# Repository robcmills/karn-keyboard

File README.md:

# karn-keyboard

Split, ortholinear, non-staggered, 38 key keyboard.

What makes the Karn unique are the 1.5u thumb arc and pinky reach keys.

### Thumb Arc Keys

I didn't like "tucking" my thumb under my palm, and most other keyboards I found in this "Ferris" family of split, minimal keyboards have thumb keys located "inside" of the homing fj keys' column. 

The Karn aligns the inner thumb key with the homing column. This feels comfortable to me, and provides a sense of "homing" to my thumbs as well. With the additional thumb keys splaying out inwards from there, in a more aggresive downward arc than the Ferris. This arc follows the natural arc of my thumb. I took photos and did measurements.

Also, the thumb keys are designed for vertical 1.5u keycaps. This is because I found 1u keycaps uncomfortable for my thumbs, as I typically make contact with the side of my thumb, which has more surface area making contact, and the sharp edge of 1u keycaps would dig into the center of the area of skin making contact. 

Other keyboards are designed with maybe one or two larger thumb keys, but they are typically 2u, which means the added complexity of stabilizers, in addition to just feeling too big.

### Pinky Reach Keys

"Pinky reach" meaning the keys in the colmn "outside" of the pinky column. On a traditional keyboard this would correspond to the Escape, Tab, Caps-lock, and Shift keys on the left hand for example. The other keyboard designs I saw either had no pinky reach keys, or a full set of three or four. The Karn is designed very much in the "all keys within one key distance of home" style, as is common in the less than 40% category. However, although the pinky diagonal reaches technically still count as "one key distance", that reach felt too difficult to me. And so they are omitted, but having zero pinky reach keys, I found it difficult to fit Tab and Enter elsewhere. There were just too few keys at that point, and so I wanted to retain a single horizontal pinky reach key on each side. I use these for Tab (left), Enter (right), and hold for Hyper. 

### Versions

There are actually two versions in this repo: 

### Karn-1

The original version is designed to be wireless. It is built around a standard 24 pin microcontroller with bluetooth support. I used the Nice-Nano-v2. With only 24 pins and 38 keys, this necessitated a matrix key layout, with diodes. Additionally, it adds an on/off switch, reset switch, and battery connector. This makes assembly much more complicated. Especially the diodes, which are super tiny, and very difficult to hot-air solder onto the tiny pads. This is not for beginners.

Also, the original karn pcb is split across two different designs, one for the left and another for the right. This doubles manufactoring costs, since you have to order the pcbs for both sides. I was learning.

### Karn-2

The karn-2 seeks to improve on the original with a host of simplifications. It is built around a 40 pin microcontroller so that there is no need for a key matrix, and hence no diodes. Furthermore, the microcontroller I found has a reset switch built onto the board, so no extra parts and hot-air soldering required. The microcontroller does not support Bluetooth, but this means no battery connector and no on/off switch. This greatly simplifies the design and assembly, and reduces the number of parts required and thus the cost.

And lastly, the karn-2 PCB is designed to be reversible, so you only need to order it once, and you can use it for both left and right. 

### Parts List

- key switches
https://mkultra.click/choc-switches
Kailh Low Profile Choc v1

- key caps
https://mkultra.click/mbk-choc-keycaps

- microcontroller (karn-1)
https://mkultra.click/nice-nano-v2/
(includes 301230 110mAh Battery with JST Connector) 

- microcontroller (karn-2)
https://www.digikey.com/en/products/detail/dfrobot/DFR0864/14824968
DFRobot Blackpill development board

- microcontroller sockets and pins (karn-1)
https://mkultra.click/mill-max-micro-controller-sockets-and-pins/

- microcontroller sockets and pins (karn-2)
https://www.digikey.com/en/products/detail/mill-max-manufacturing-corp/315-43-120-41-003000/4455248
Mill-max 315-43-120-41-003000 sockets
https://www.digikey.com/en/products/detail/mill-max-manufacturing-corp/3320-1-00-15-00-00-03-0/4147393
Mill-max 3320-1-00-15-00-00-03-0 pins

- trrs jack
https://mkultra.click/pj-320a-3-5mm-trrs-jack/

- power switches (karn-1)
https://mkultra.click/alps-ssss811101/
https://tech.alpsalpine.com/e/products/detail/SSSS811101/

- diodes (karn-1)
https://www.digikey.com/en/products/detail/micro-commercial-co/1N4148X-TP/789328
PART: 1N4148XTPMSCT-ND
MFG : MICRO COMMERCIAL CO (VA) / 1N4148X-TP
DESC: DIODE GEN PURP 75V 150MA SOD523
UNIT PRICE: $0.173

- leds (karn-1)
https://www.digikey.com/en/products/detail/adafruit-industries-llc/2686/5804107
PART: 1528-1541-ND
MFG : ADAFRUIT INDUSTRIES LLC / 2686
DESC: ADDRESS LED DISC SERIAL RGB 10PK
UNIT PRICE: $4.95 (for quantity 10)

- battery connectors (karn-1)
https://www.digikey.com/en/products/detail/jst-sales-america-inc/S2B-PH-K-S-LF-SN/926626
PART: 455-1719-ND
MFG : JST SALES AMERICA INC / S2B-PH-K-S(LF)(SN)
DESC: CONN HEADER R/A 2POS 2MM
UNIT PRICE: $0.134

- reset switches (karn-1)
https://www.digikey.com/en/products/detail/e-switch/TL3313AF250QG/4029401
PART: EG6065CT-ND
MFG : E-SWITCH (VA) / TL3313AF250QG
DESC: SWITCH TACTILE SPST-NO 0.05A 12V
UNIT PRICE: $0.431

- feet
Self-Adhesive Clear Rubber Feet Tiny Bumpons (6x2mm)
https://www.amazon.com/dp/B06XCNM69B

- pcb
https://www.pcbway.com/

### Firmware

https://github.com/robcmills/karn-keyboard-firmware

### Inspiration

#### Thumb Block Style

- Maltron https://en.wikipedia.org/wiki/Maltron

- Kinesis Advantage https://kinesis-ergo.com/shop/advantage2/

- Ergodox EZ https://ergodox-ez.com/

#### Thumb Arc Style

- NEC PWP http://xahlee.info/kbd/nec_pc-8801_keyboard.html

- Kyria https://blog.splitkb.com/blog/introducing-the-kyria

- Corne https://github.com/foostan/crkbd

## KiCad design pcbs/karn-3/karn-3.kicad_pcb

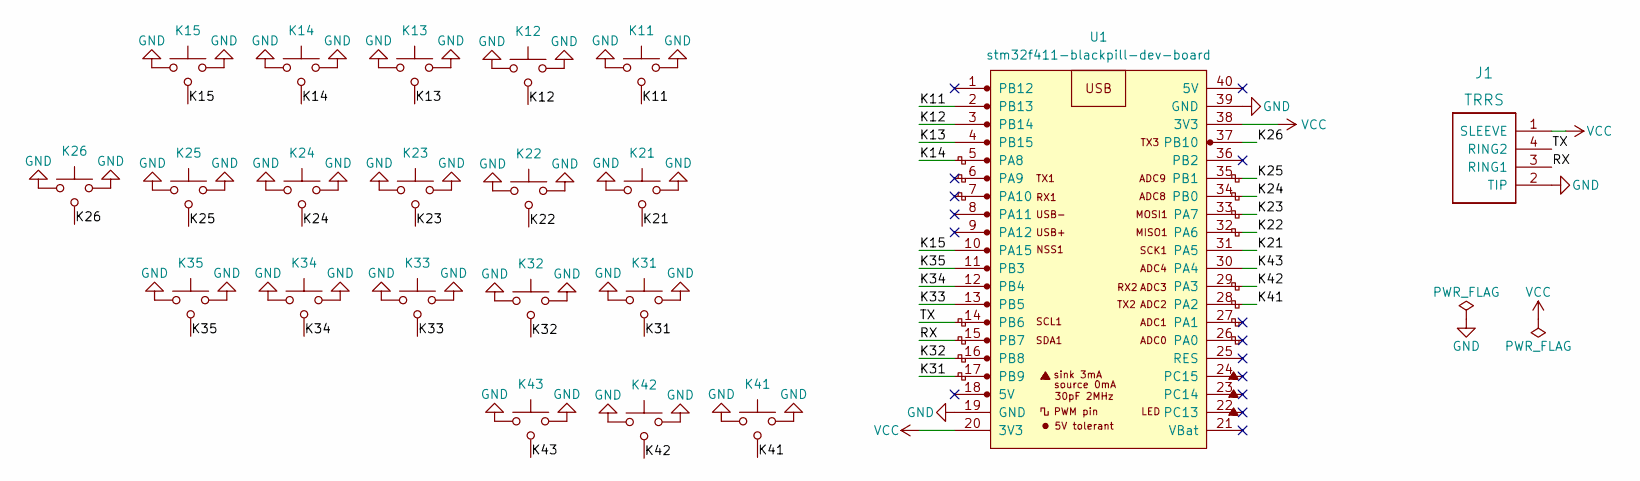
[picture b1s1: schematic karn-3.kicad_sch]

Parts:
J1: TRRS; trrs-pj-320A
K11, K12, K13, K14, K15, K21, K22, K23, K24, K25, K31, K32, K33, K34, K35: SW_Push; kailh-choc-v1-1u-MBK-keycap
K26, K41, K42, K43: SW_Push_1.5; kailh-choc-v1-1_5u-MBK-keycap
U1: stm32f411-blackpill-dev-board

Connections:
/K11: K11.1, U1.2 (PB13); also elsewhere on the board
/K12: K12.1, U1.3 (PB14); also elsewhere on the board
/K13: K13.1, U1.4 (PB15); also elsewhere on the board
/K14: K14.1, U1.5 (PA8); also elsewhere on the board
/K15: K15.1, U1.10 (PA15); also elsewhere on the board
/K21: K21.1, U1.31 (PA5); also elsewhere on the board
/K22: K22.1, U1.32 (PA6); also elsewhere on the board
/K23: K23.1, U1.33 (PA7); also elsewhere on the board
/K24: K24.1, U1.34 (PB0); also elsewhere on the board
/K25: K25.1, U1.35 (PB1); also elsewhere on the board
/K26: K26.1, U1.37 (PB10); also elsewhere on the board
/K31: K31.1, U1.17 (PB9); also elsewhere on the board
/K32: K32.1, U1.16 (PB8); also elsewhere on the board
/K33: K33.1, U1.13 (PB5); also elsewhere on the board
/K34: K34.1, U1.12 (PB4); also elsewhere on the board
/K35: K35.1, U1.11 (PB3); also elsewhere on the board
/K41: K41.1, U1.28 (PA2); also elsewhere on the board
/K42: K42.1, U1.29 (PA3); also elsewhere on the board
/K43: K43.1, U1.30 (PA4); also elsewhere on the board
/RX: J1.3 (RING2), U1.15 (PB7); also elsewhere on the board
/TX: J1.4 (RING1), U1.14 (PB6); also elsewhere on the board
GND: J1.2 (TIP), K11.2, K11.3, K12.2, K12.3, K13.2, K13.3, K14.2, K14.3, K15.2, K15.3, K21.2, K21.3, K22.2, K22.3, K23.2, K23.3, K24.2, K24.3, K25.2, K25.3, K26.2, K26.3, K31.2, K31.3, K32.2, K32.3, K33.2, K33.3, K34.2, K34.3, K35.2, K35.3, K41.2, K41.3, K42.2, K42.3, K43.2, K43.3, U1.19 (GND), U1.39 (GND); also elsewhere on the board
VCC: J1.1 (SLEEVE), U1.20 (3V3), U1.38 (3V3); also elsewhere on the board

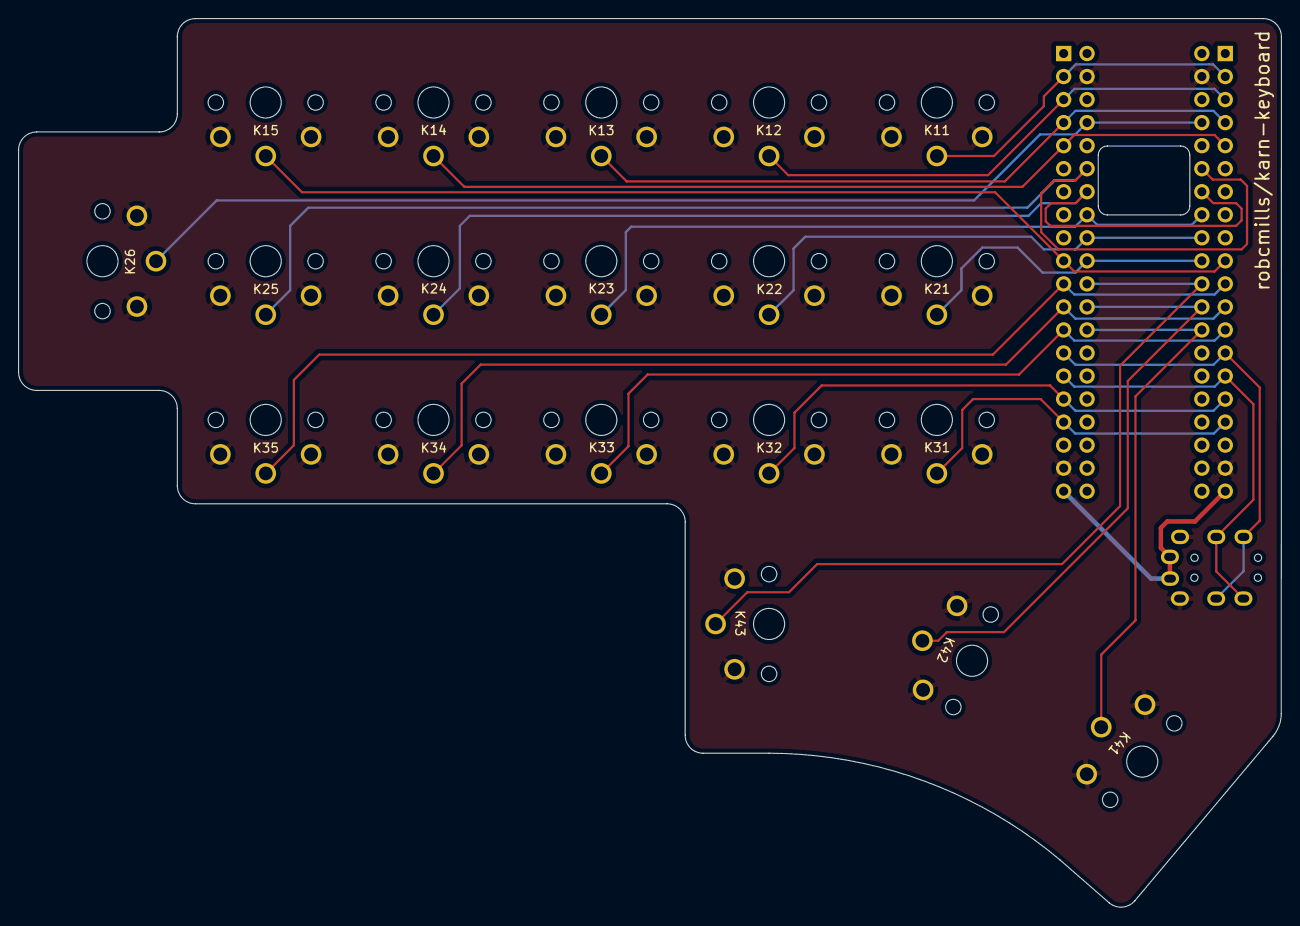
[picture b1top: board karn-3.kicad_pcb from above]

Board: 2 copper layers, 139.2 x 98.0 mm, 22 parts (1 on the bottom side), 23 nets.

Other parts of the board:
U2: WeAct BlackPill; stm32f411-blackpill-dev-board

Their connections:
/K11: U2.2; also elsewhere on the board
/K12: U2.3; also elsewhere on the board
/K13: U2.4; also elsewhere on the board
/K14: U2.5; also elsewhere on the board
/K15: U2.10; also elsewhere on the board
/K21: U2.31; also elsewhere on the board
/K22: U2.32; also elsewhere on the board
/K23: U2.33; also elsewhere on the board
/K24: U2.34; also elsewhere on the board
/K25: U2.35; also elsewhere on the board
/K26: U2.37; also elsewhere on the board
/K31: U2.17; also elsewhere on the board
/K32: U2.16; also elsewhere on the board
/K33: U2.13; also elsewhere on the board
/K34: U2.12; also elsewhere on the board
/K35: U2.11; also elsewhere on the board
/K41: U2.28; also elsewhere on the board
/K42: U2.29; also elsewhere on the board
/K43: U2.30; also elsewhere on the board
/RX: U2.15; also elsewhere on the board
/TX: U2.14; also elsewhere on the board
GND: U2.19, U2.39; also elsewhere on the board
VCC: U2.20; also elsewhere on the board

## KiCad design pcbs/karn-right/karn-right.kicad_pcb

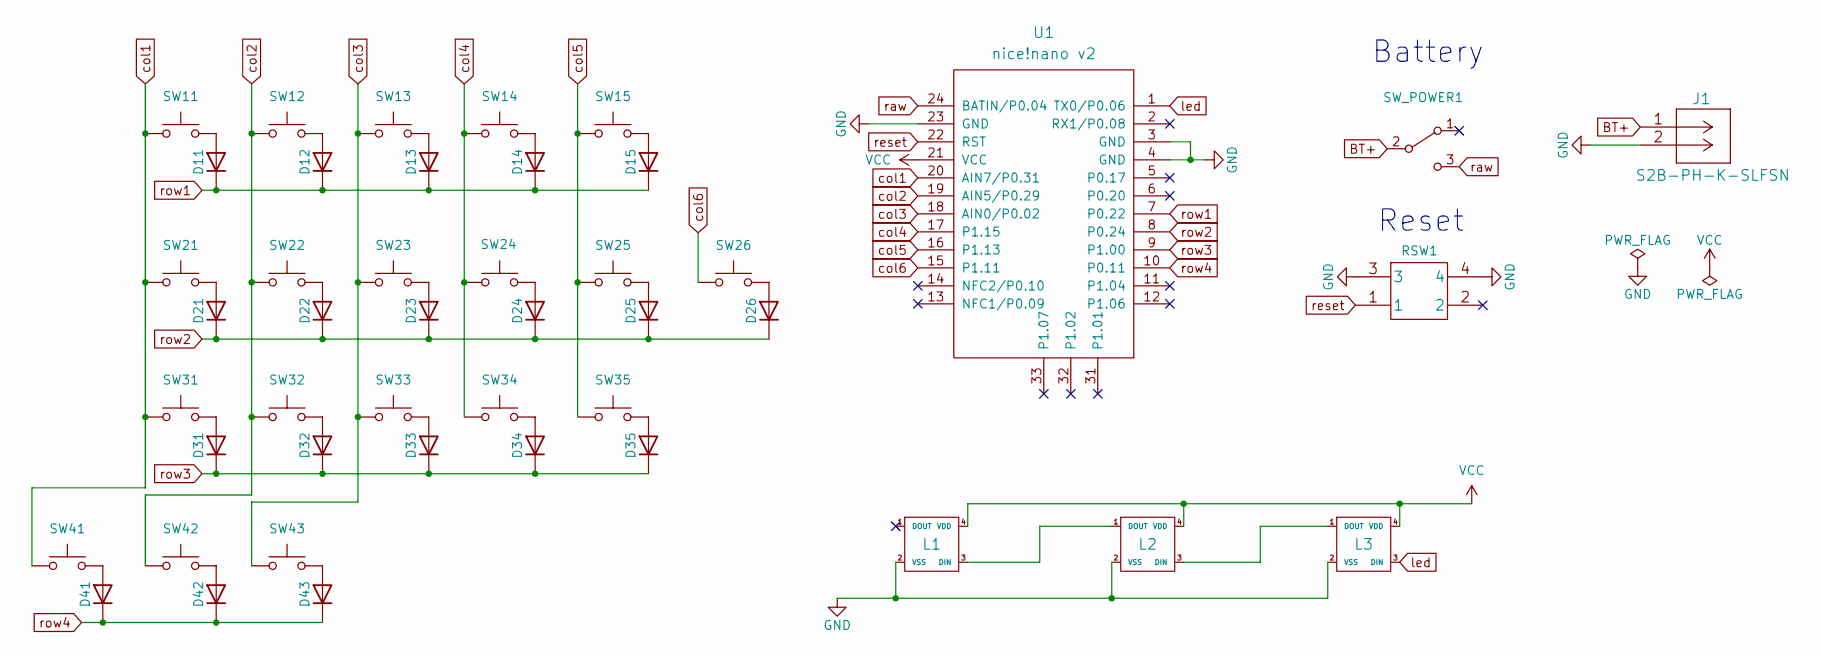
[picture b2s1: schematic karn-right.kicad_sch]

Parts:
D11, D12, D13, D14, D15, D21, D22, D23, D24, D25, D26, D31, D32, D33, D34, D35, D41, D42, D43: D; 1N4148X-TP
J1: S2B-PH-K-SLFSN; CONN_S2B-PH-K-S_JST
L1, L2, L3: SK6812MINI; LED_SK6812MINI_PLCC4_3.5x3.5mm_P1.75mm
RSW1: SW_Push; reset-switch-TL3313AF250QG
SW11, SW12, SW13, SW14, SW15, SW21, SW22, SW23, SW24, SW25, SW31, SW32, SW33, SW34, SW35: SW_Push; MBK choc 1u
SW26, SW41, SW42, SW43: SW_Push; MBK choc 1.5u
SW_POWER1: SW_SPDT; SW_SPDT_PCM12
U1: nice!nano v2; nice_nano

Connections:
BT+: J1.1, SW_POWER1.2 (B)
GND: J1.2, L1.2 (VSS), L2.2 (VSS), L3.2 (VSS), RSW1.3, RSW1.4, U1.3 (GND), U1.4 (GND), U1.23 (GND)
unnamed: D11.2 (A), SW11.2
unnamed: D12.2 (A), SW12.2
unnamed: D13.2 (A), SW13.2
unnamed: D14.2 (A), SW14.2
unnamed: D15.2 (A), SW15.2
unnamed: D21.2 (A), SW21.2
unnamed: D22.2 (A), SW22.2
unnamed: D23.2 (A), SW23.2
unnamed: D24.2 (A), SW24.2
unnamed: D25.2 (A), SW25.2
unnamed: D26.2 (A), SW26.2
unnamed: D31.2 (A), SW31.2
unnamed: D32.2 (A), SW32.2
unnamed: D33.2 (A), SW33.2
unnamed: D34.2 (A), SW34.2
unnamed: D35.2 (A), SW35.2
unnamed: D41.2 (A), SW41.2
unnamed: D42.2 (A), SW42.2
unnamed: D43.2 (A), SW43.2
unnamed: L1.3 (DIN), L2.1 (DOUT)
unnamed: L2.3 (DIN), L3.1 (DOUT)
VCC: L1.4 (VDD), L2.4 (VDD), L3.4 (VDD), U1.21 (VCC)
col1: SW11.1, SW21.1, SW31.1, SW41.1, U1.20 (AIN7/P0.31)
col2: SW12.1, SW22.1, SW32.1, SW42.1, U1.19 (AIN5/P0.29)
col3: SW13.1, SW23.1, SW33.1, SW43.1, U1.18 (AIN0/P0.02)
col4: SW14.1, SW24.1, SW34.1, U1.17 (P1.15)
col5: SW15.1, SW25.1, SW35.1, U1.16 (P1.13)
col6: SW26.1, U1.15 (P1.11)
led: L3.3 (DIN), U1.1 (TX0/P0.06)
raw: SW_POWER1.3 (C), U1.24 (BATIN/P0.04)
reset: RSW1.1, U1.22 (RST)
row1: D11.1 (K), D12.1 (K), D13.1 (K), D14.1 (K), D15.1 (K), U1.7 (P0.22)
row2: D21.1 (K), D22.1 (K), D23.1 (K), D24.1 (K), D25.1 (K), D26.1 (K), U1.8 (P0.24)
row3: D31.1 (K), D32.1 (K), D33.1 (K), D34.1 (K), D35.1 (K), U1.9 (P1.00)
row4: D41.1 (K), D42.1 (K), D43.1 (K), U1.10 (P0.11)

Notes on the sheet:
Reset
Battery

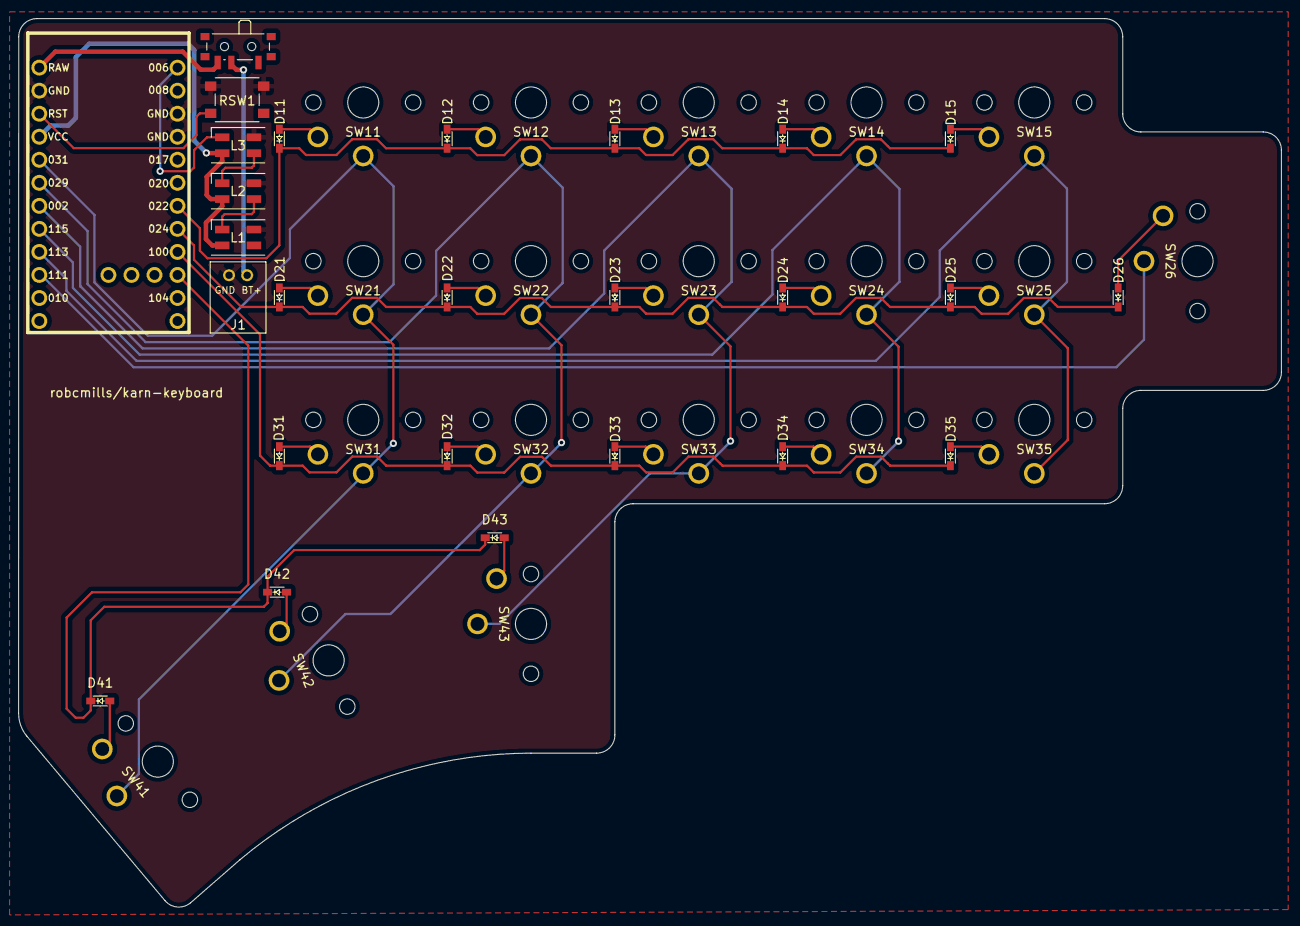
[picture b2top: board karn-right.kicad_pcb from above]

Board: 2 copper layers, 139.3 x 98.0 mm, 45 parts (1 on the bottom side), 37 nets.

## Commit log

2022-09-13 Add schematic first draft
2022-09-14 Update PCB from schematic first draft
2022-09-15 Various changes:
    - Add start of parts list
    - Fix impossible placement of diodes
2022-09-18 Add first draft of routing
2022-09-18 Add gnd planes
2022-09-20 karn-right v1 with gerber files
2022-09-25 Add karn-left PCB
2022-10-01 Add led spec sheet pdf
2022-10-01 Add images dir
2022-10-05 Various changes:
    - Fix incorrect reset-switch-TL3313 symbol and footprint
    - Increase size of diode footprint pads
2022-10-08 Update gerbers and add screenshots
2022-10-16 Small update to README
2022-10-17 Update karn-left pcb
    - Apply various fixes from lessons learned on karn-right
    - Fix incorrectly oriented reset switch
    - Swap incorrect default polarity of JST connector footprint
    - Increase size of diode pads
2022-10-17 Add images to README
2022-10-17 Fix image extension
2022-10-17 Add link to firmware repo
2022-10-30 Rename components dir to specs
2022-11-03 Add completed image of both left and right
2022-11-05 Add inspiration section to readme
2022-12-27 Update karn-left-backups
2022-12-31 Add in-progress start of karn-2
2023-01-07 Add karn-2 gerber files
2023-01-07 Add karn-2 section to readme
2023-02-14 Add karn-2 photos
2025-05-16 Duplicate karn-2 to karn-3
